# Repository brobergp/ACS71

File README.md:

# ACS71
Custom keyboard, OEM PI Pico based.

This rep is not complete, for the moment it contains the kicad schematic and pcb files as the YAML for Ergogen, the body is not finalized but when it is the STL and CAD files will be here as well. And When complete I will add my KMK keymap as well for future reference.

Kailh Hotswap sockets, SK6812mini-E Leds, 1N4148SOD-123 diodes

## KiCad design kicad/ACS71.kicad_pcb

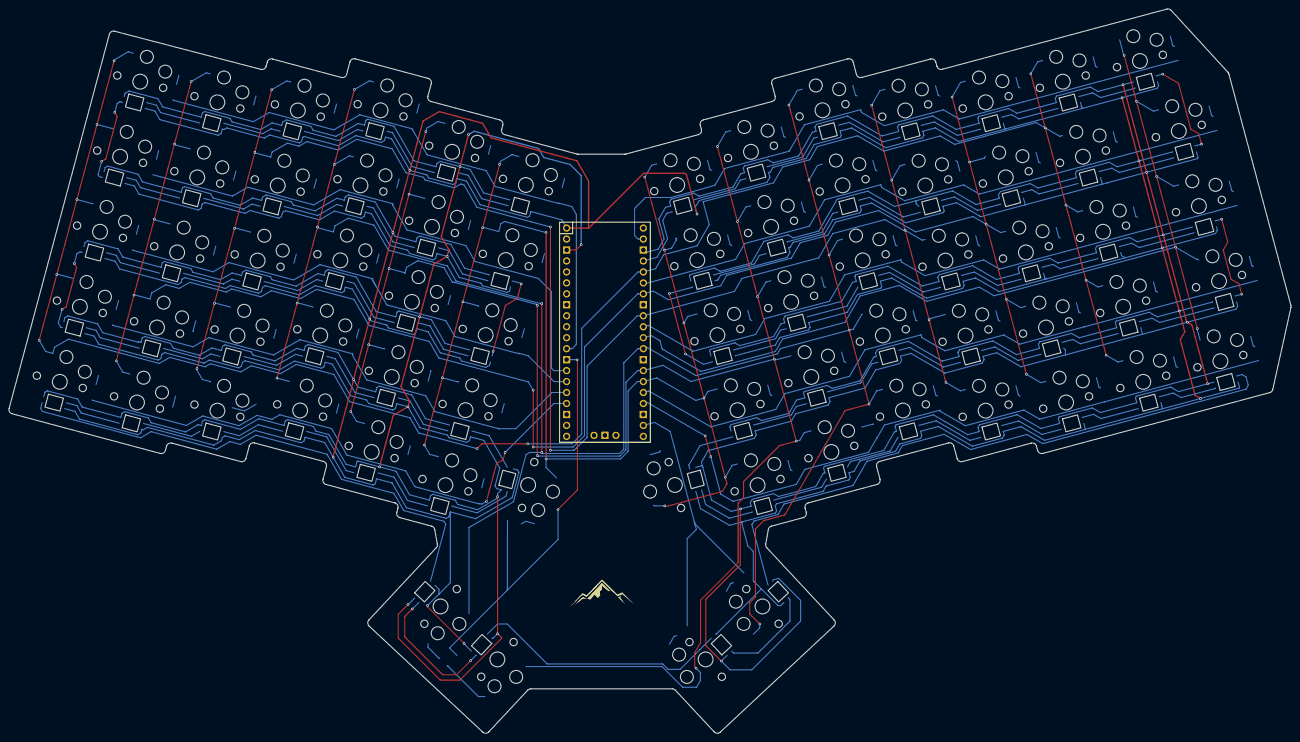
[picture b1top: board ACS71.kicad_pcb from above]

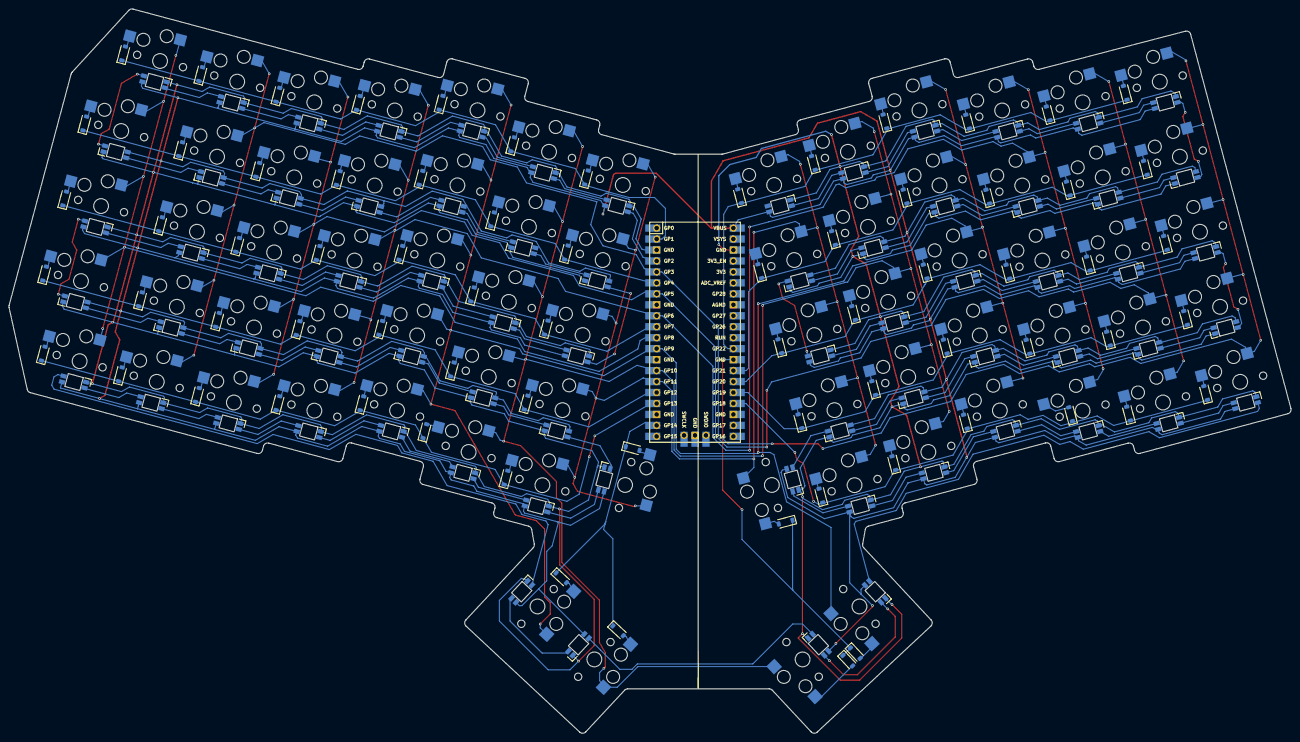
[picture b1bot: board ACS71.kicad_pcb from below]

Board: 2 copper layers, 297.0 x 167.8 mm, 214 parts (143 on the bottom side), 22 nets.

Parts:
D1, D2, D3, D4, D5, D6, D7, D8, D9, D10, D11, D12, D13, D14, D15, D16, D17, D18, D19, D20, D21, D22, D23, D24, D25, D26, D27, D28, D29, D30, D31, D32, D33, D34, D35, D36, D37, D38, D39, D40, D41, D42, D43, D44, D45, D46, D47, D48, D49, D50, D51, D52, D53, D54, D55, D56, D57, D58, D59, D60, D61, D62, D63, D64, D65, D66, D67, D68, D69, D70, D71: D_SOD-123
LED1, LED2, LED3, LED4, LED5, LED6, LED7, LED8, LED9, LED10, LED11, LED12, LED13, LED14, LED15, LED16, LED17, LED18, LED19, LED20, LED21, LED22, LED23, LED24, LED25, LED26, LED27, LED28, LED29, LED30, LED31, LED32, LED33, LED34, LED35, LED36, LED37, LED38, LED39, LED40, LED41, LED42, LED43, LED44, LED45, LED46, LED47, LED48, LED49, LED50, LED51, LED52, LED53, LED54, LED55, LED56, LED57, LED58, LED59, LED60, LED61, LED62, LED63, LED64, LED65, LED66, LED67, LED68, LED69, LED70, LED71: led_SK6812mini-e (per-keysingle-side)
S1, S2, S3, S4, S5, S6, S7, S8, S9, S10, S11, S12, S13, S14, S15, S16, S17, S18, S19, S20, S21, S22, S23, S24, S25, S26, S27, S28, S29, S30, S31, S32, S33, S34, S35, S36, S37, S38, S39, S40, S41, S42, S43, S44, S45, S46, S47, S48, S49, S50, S51, S52, S53, S54, S55, S56, S57, S58, S59, S60, S61, S62, S63, S64, S65, S66, S67, S68, S69, S70, S71: PG1350
U1: Raspberry_Pi_Pico

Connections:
COLUMN1: S1.1, S2.1, S3.1, S4.1, S5.1, S6.1, S39.1, S40.1, S41.1, S42.1, S43.1, S44.1, U1.15 (GPIO11)
COLUMN2: S7.1, S8.1, S9.1, S10.1, S11.1, S38.1, S45.1, S46.1, S47.1, S48.1, S49.1, S71.1, U1.14 (GPIO10)
COLUMN3: S12.1, S13.1, S14.1, S15.1, S16.1, S37.1, S50.1, S51.1, S52.1, S53.1, S54.1, S70.1, U1.12 (GPIO9)
COLUMN4: S17.1, S18.1, S19.1, S20.1, S21.1, S55.1, S56.1, S57.1, S58.1, S59.1, U1.9 (GPIO6)
COLUMN5: S22.1, S23.1, S24.1, S25.1, S26.1, S60.1, S61.1, S62.1, S63.1, S64.1, U1.7 (GPIO5)
COLUMN6: S27.1, S28.1, S29.1, S30.1, S31.1, S65.1, S66.1, S67.1, S68.1, S69.1, U1.5 (GPIO3)
COLUMN7: S32.1, S33.1, S34.1, S35.1, S36.1, U1.11 (GPIO8)
DIN: LED1.2, LED1.4, LED2.2, LED2.4, LED3.2, LED3.4, LED4.2, LED4.4, LED5.2, LED5.4, LED6.2, LED6.4, LED7.2, LED7.4, LED8.2, LED8.4, LED9.2, LED9.4, LED10.2, LED10.4, LED11.2, LED11.4, LED12.2, LED12.4, LED13.2, LED13.4, LED14.2, LED14.4, LED15.2, LED15.4, LED16.2, LED16.4, LED17.2, LED17.4, LED18.2, LED18.4, LED19.2, LED19.4, LED20.2, LED20.4, LED21.2, LED21.4, LED22.2, LED22.4, LED23.2, LED23.4, LED24.2, LED24.4, LED25.2, LED25.4, LED26.2, LED26.4, LED27.2, LED27.4, LED28.2, LED28.4, LED29.2, LED29.4, LED30.2, LED30.4, LED31.2, LED31.4, LED32.2, LED32.4, LED33.2, LED33.4, LED34.2, LED34.4, LED35.2, LED35.4, LED36.2, LED36.4, LED37.2, LED37.4, LED38.2, LED38.4, LED39.2, LED39.4, LED40.2, LED40.4, LED41.2, LED41.4, LED42.2, LED42.4, LED43.2, LED43.4, LED44.2, LED44.4, LED45.2, LED45.4, LED46.2, LED46.4, LED47.2, LED47.4, LED48.2, LED48.4, LED49.2, LED49.4, LED50.2, LED50.4, LED51.2, LED51.4, LED52.2, LED52.4, LED53.2, LED53.4, LED54.2, LED54.4, LED55.2, LED55.4, LED56.2, LED56.4, LED57.2, LED57.4, LED58.2, LED58.4, LED59.2, LED59.4, LED60.2, LED60.4, LED61.2, LED61.4, LED62.2, LED62.4, LED63.2, LED63.4, LED64.2, LED64.4, LED65.2, LED65.4, LED66.2, LED66.4, LED67.2, LED67.4, LED68.2, LED68.4, LED69.2, LED69.4, LED70.2, LED70.4, LED71.2, LED71.4, U1.4 (GPIO2)
GND: LED1.3, LED2.3, LED3.3, LED4.3, LED5.3, LED6.3, LED7.3, LED8.3, LED9.3, LED10.3, LED11.3, LED12.3, LED13.3, LED14.3, LED15.3, LED16.3, LED17.3, LED18.3, LED19.3, LED20.3, LED21.3, LED22.3, LED23.3, LED24.3, LED25.3, LED26.3, LED27.3, LED28.3, LED29.3, LED30.3, LED31.3, LED32.3, LED33.3, LED34.3, LED35.3, LED36.3, LED37.3, LED38.3, LED39.3, LED40.3, LED41.3, LED42.3, LED43.3, LED44.3, LED45.3, LED46.3, LED47.3, LED48.3, LED49.3, LED50.3, LED51.3, LED52.3, LED53.3, LED54.3, LED55.3, LED56.3, LED57.3, LED58.3, LED59.3, LED60.3, LED61.3, LED62.3, LED63.3, LED64.3, LED65.3, LED66.3, LED67.3, LED68.3, LED69.3, LED70.3, LED71.3, U1.3 (GND), U1.23 (GND), U1.38 (GND)
ROW1: D6.1, D6.2, D11.1, D11.2, D16.1, D16.2, D21.1, D21.2, D26.1, D26.2, D31.1, D31.2, D36.1, D36.2, S6.2, S11.2, S16.2, S21.2, S26.2, S31.2, S36.2, U1.2 (GPIO1)
ROW2: D5.1, D5.2, D10.1, D10.2, D15.1, D15.2, D20.1, D20.2, D25.1, D25.2, D30.1, D30.2, D35.1, D35.2, S5.2, S10.2, S15.2, S20.2, S25.2, S30.2, S35.2, U1.6 (GPIO4)
ROW3: D4.1, D4.2, D9.1, D9.2, D14.1, D14.2, D19.1, D19.2, D24.1, D24.2, D29.1, D29.2, D34.1, D34.2, S4.2, S9.2, S14.2, S19.2, S24.2, S29.2, S34.2, U1.10 (GPIO7)
ROW4: D3.1, D3.2, D8.1, D8.2, D13.1, D13.2, D18.1, D18.2, D23.1, D23.2, D28.1, D28.2, D33.1, D33.2, S3.2, S8.2, S13.2, S18.2, S23.2, S28.2, S33.2, U1.16 (GPIO12)
ROW5: D2.1, D2.2, D7.1, D7.2, D12.1, D12.2, D17.1, D17.2, D22.1, D22.2, D27.1, D27.2, D32.1, D32.2, S2.2, S7.2, S12.2, S17.2, S22.2, S27.2, S32.2, U1.17 (GPIO13)
ROW6: D1.1, D1.2, D37.1, D37.2, D38.1, D38.2, S1.2, S37.2, S38.2, U1.19 (GPIO14)
ROW7: D44.1, D44.2, D49.1, D49.2, D54.1, D54.2, D59.1, D59.2, D64.1, D64.2, D69.1, D69.2, S44.2, S49.2, S54.2, S59.2, S64.2, S69.2, U1.29 (GPIO22)
ROW8: D43.1, D43.2, D48.1, D48.2, D53.1, D53.2, D58.1, D58.2, D63.1, D63.2, D68.1, D68.2, S43.2, S48.2, S53.2, S58.2, S63.2, S68.2, U1.27 (GPIO21)
ROW9: D42.1, D42.2, D47.1, D47.2, D52.1, D52.2, D57.1, D57.2, D62.1, D62.2, D67.1, D67.2, S42.2, S47.2, S52.2, S57.2, S62.2, S67.2, U1.26 (GPIO20)
ROW10: D41.1, D41.2, D46.1, D46.2, D51.1, D51.2, D56.1, D56.2, D61.1, D61.2, D66.1, D66.2, S41.2, S46.2, S51.2, S56.2, S61.2, S66.2, U1.25 (GPIO19)
ROW11: D40.1, D40.2, D45.1, D45.2, D50.1, D50.2, D55.1, D55.2, D60.1, D60.2, D65.1, D65.2, S40.2, S45.2, S50.2, S55.2, S60.2, S65.2, U1.24 (GPIO18)
ROW12: D39.1, D39.2, D70.1, D70.2, D71.1, D71.2, S39.2, S70.2, S71.2, U1.28 (GND)
VBUS: LED1.1, LED2.1, LED3.1, LED4.1, LED5.1, LED6.1, LED7.1, LED8.1, LED9.1, LED10.1, LED11.1, LED12.1, LED13.1, LED14.1, LED15.1, LED16.1, LED17.1, LED18.1, LED19.1, LED20.1, LED21.1, LED22.1, LED23.1, LED24.1, LED25.1, LED26.1, LED27.1, LED28.1, LED29.1, LED30.1, LED31.1, LED32.1, LED33.1, LED34.1, LED35.1, LED36.1, LED37.1, LED38.1, LED39.1, LED40.1, LED41.1, LED42.1, LED43.1, LED44.1, LED45.1, LED46.1, LED47.1, LED48.1, LED49.1, LED50.1, LED51.1, LED52.1, LED53.1, LED54.1, LED55.1, LED56.1, LED57.1, LED58.1, LED59.1, LED60.1, LED61.1, LED62.1, LED63.1, LED64.1, LED65.1, LED66.1, LED67.1, LED68.1, LED69.1, LED70.1, LED71.1, U1.40 (VBUS)

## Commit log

2024-11-24 Update ACS71-Ergogen.yaml
    Ergogen YAML file
